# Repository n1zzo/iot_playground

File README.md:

# IoT Playground
## Experiment with ESP32 and Micropython

This repository contains instructions and code examples on the MicroPython framework used on an ESP32 board.

The combination of these two elements allows newcomers to learn and build the Internet of Things using
a simple and coherent platform, yet very powerful.

All the setup instructions and code examples can be found on [the wiki](https://github.com/n1zzo/iot_playground/wiki).

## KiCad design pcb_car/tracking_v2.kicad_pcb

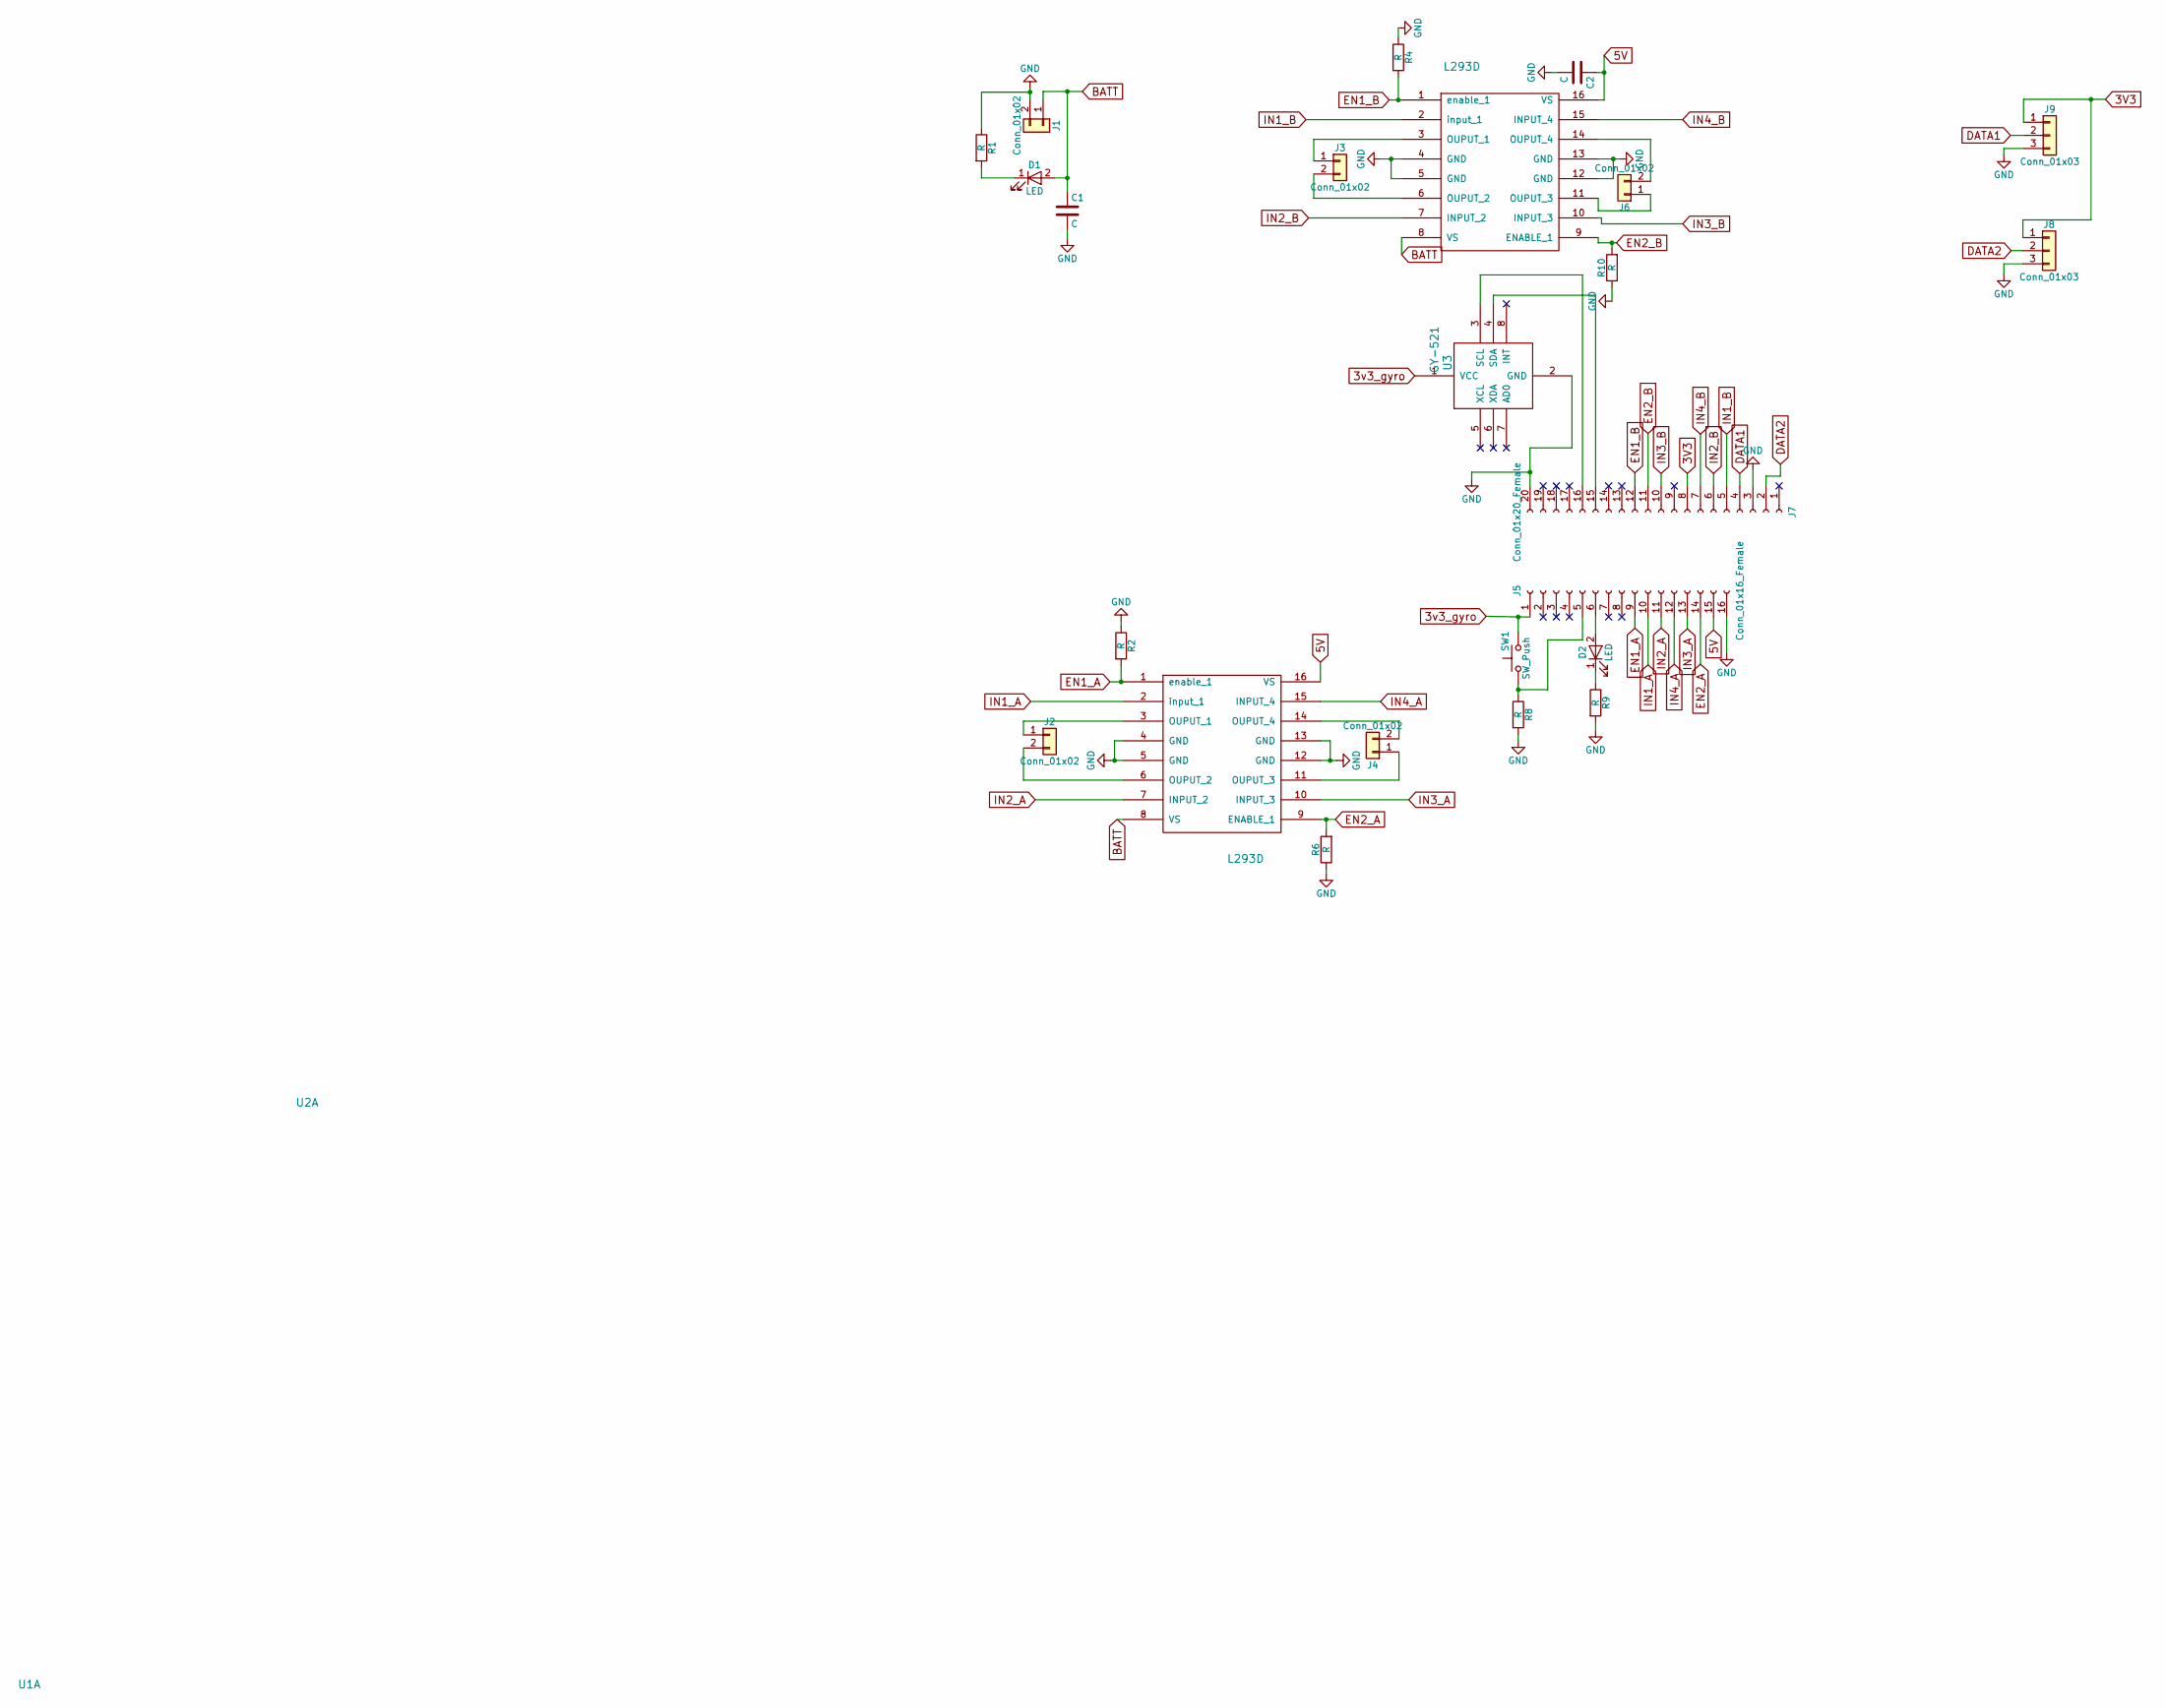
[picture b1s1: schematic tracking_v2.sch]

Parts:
C1, C2: C; C_1206_HandSoldering
D1, D2: LED; LED_0805_HandSoldering
J1, J2, J3, J4, J6: Conn_01x02; Pin_Header_Straight_1x02_Pitch2.54mm
J5: Conn_01x16_Female; Socket_Strip_Straight_1x16_Pitch2.54mm
J7: Conn_01x20_Female; Socket_Strip_Straight_1x20_Pitch2.54mm
J8, J9: Conn_01x03; Pin_Header_Straight_1x03_Pitch2.54mm
R1, R2, R4, R6, R8, R9, R10: R; R_1206_HandSoldering
SW1: SW_Push; SW_SPST_EVPBF
U1, U2: L293D; DIL16
U3: GY-521

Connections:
3V3: J7.8, J8.1, J9.1
3v3_gyro: J5.1, SW1.2, U3.1 (VCC)
5V: C2.1, J5.15, U1.16 (VS), U2.16 (VS)
BATT: C1.1, D1.2 (A), J1.1, U1.8 (VS), U2.8 (VS)
DATA1: J7.4, J9.2
DATA2: J7.2, J8.2
EN1_A: J5.9, R2.2, U1.1 (enable_1)
EN1_B: J7.12, R4.2, U2.1 (enable_1)
EN2_A: J5.14, R6.2, U1.9 (ENABLE_1)
EN2_B: J7.11, R10.2, U2.9 (ENABLE_1)
GND: C1.2, C2.2, J1.2, J5.16, J7.3, J7.20, J8.3, J9.3, R1.1, R2.1, R4.1, R6.1, R8.2, R9.2, R10.1, U1.4 (GND), U1.5 (GND), U1.12 (GND), U1.13 (GND), U2.4 (GND), U2.5 (GND), U2.12 (GND), U2.13 (GND), U3.2 (GND)
IN1_A: J5.10, U1.2 (input_1)
IN1_B: J7.5, U2.2 (input_1)
IN2_A: J5.11, U1.7 (INPUT_2)
IN2_B: J7.6, U2.7 (INPUT_2)
IN3_A: J5.13, U1.10 (INPUT_3)
IN3_B: J7.10, U2.10 (INPUT_3)
IN4_A: J5.12, U1.15 (INPUT_4)
IN4_B: J7.7, U2.15 (INPUT_4)
unnamed: D1.1 (K), R1.2
unnamed: D2.1 (K), R9.1
unnamed: D2.2 (A), J5.6
unnamed: J2.1, U1.3 (OUPUT_1)
unnamed: J2.2, U1.6 (OUPUT_2)
unnamed: J3.1, U2.3 (OUPUT_1)
unnamed: J3.2, U2.6 (OUPUT_2)
unnamed: J4.1, U1.11 (OUPUT_3)
unnamed: J4.2, U1.14 (OUPUT_4)
unnamed: J5.5, R8.1, SW1.1
unnamed: J6.1, U2.11 (OUPUT_3)
unnamed: J6.2, U2.14 (OUPUT_4)
unnamed: J7.15, U3.4 (SDA)
unnamed: J7.16, U3.3 (SCL)

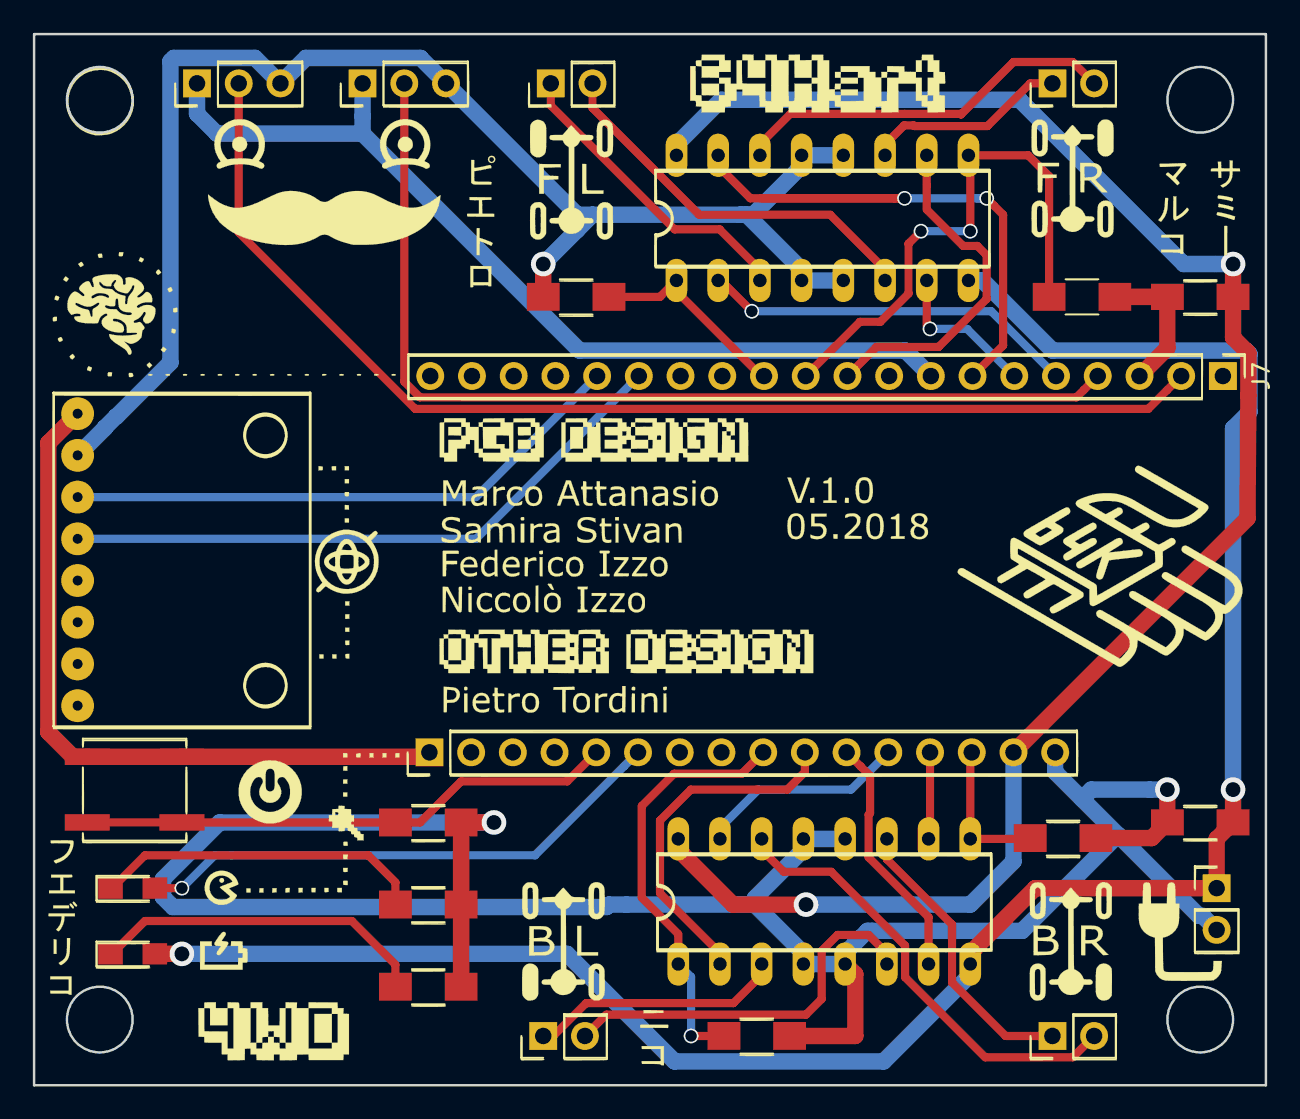
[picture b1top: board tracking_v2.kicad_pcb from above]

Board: 2 copper layers, 75.0 x 64.0 mm, 24 parts (0 on the bottom side), 33 nets.

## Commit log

2018-02-01 Add readme.
2018-02-01 Update README, add scripts.
2018-02-05 Add code for heart rate sensor.
2018-02-07 Update hear rate algorithm.
2018-02-07 Add Net class implementation.
2018-02-16 added temperature sensor
2018-02-21 Update net class with get method.
2018-02-22 Add slides markdown content.
2018-02-23 Updated slides.
2018-02-25 Add slides about electronics
2018-02-25 Add more slides.
2018-02-25 Add electronics 101
2018-02-25 Add electronics_2
2018-02-25 Add brainstorming slides.
2018-02-25 Add more stuff.
2018-02-25 Slides are now finished.
2018-02-27 Fix net class and add network example.
2018-05-21 code car
2018-05-22 pcb car
2018-05-22 pcb car
    updated schematic and libraries
2018-05-23 Added second iteration of PCB design (incomplete), moved libraries to subfolder
2018-05-23 Finished second iteration of PCB
2018-05-23 Minor improvements to PCB
2018-05-24 placement updated
2018-05-24 modifications for silkscreen
2018-05-24 Minor routing change to the Back layer
2018-05-24 added PCB silkscreen
2018-05-24 Removed unnecessary vias and tracks
2018-05-24 final version
    added silkscreen
2018-05-24 gerber files
2018-05-24 gerber
2018-06-08 slides corso
2018-06-09 slides
